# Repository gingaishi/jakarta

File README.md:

View this project on [CADLAB.io](https://cadlab.io/project/28195). 

# jakarta

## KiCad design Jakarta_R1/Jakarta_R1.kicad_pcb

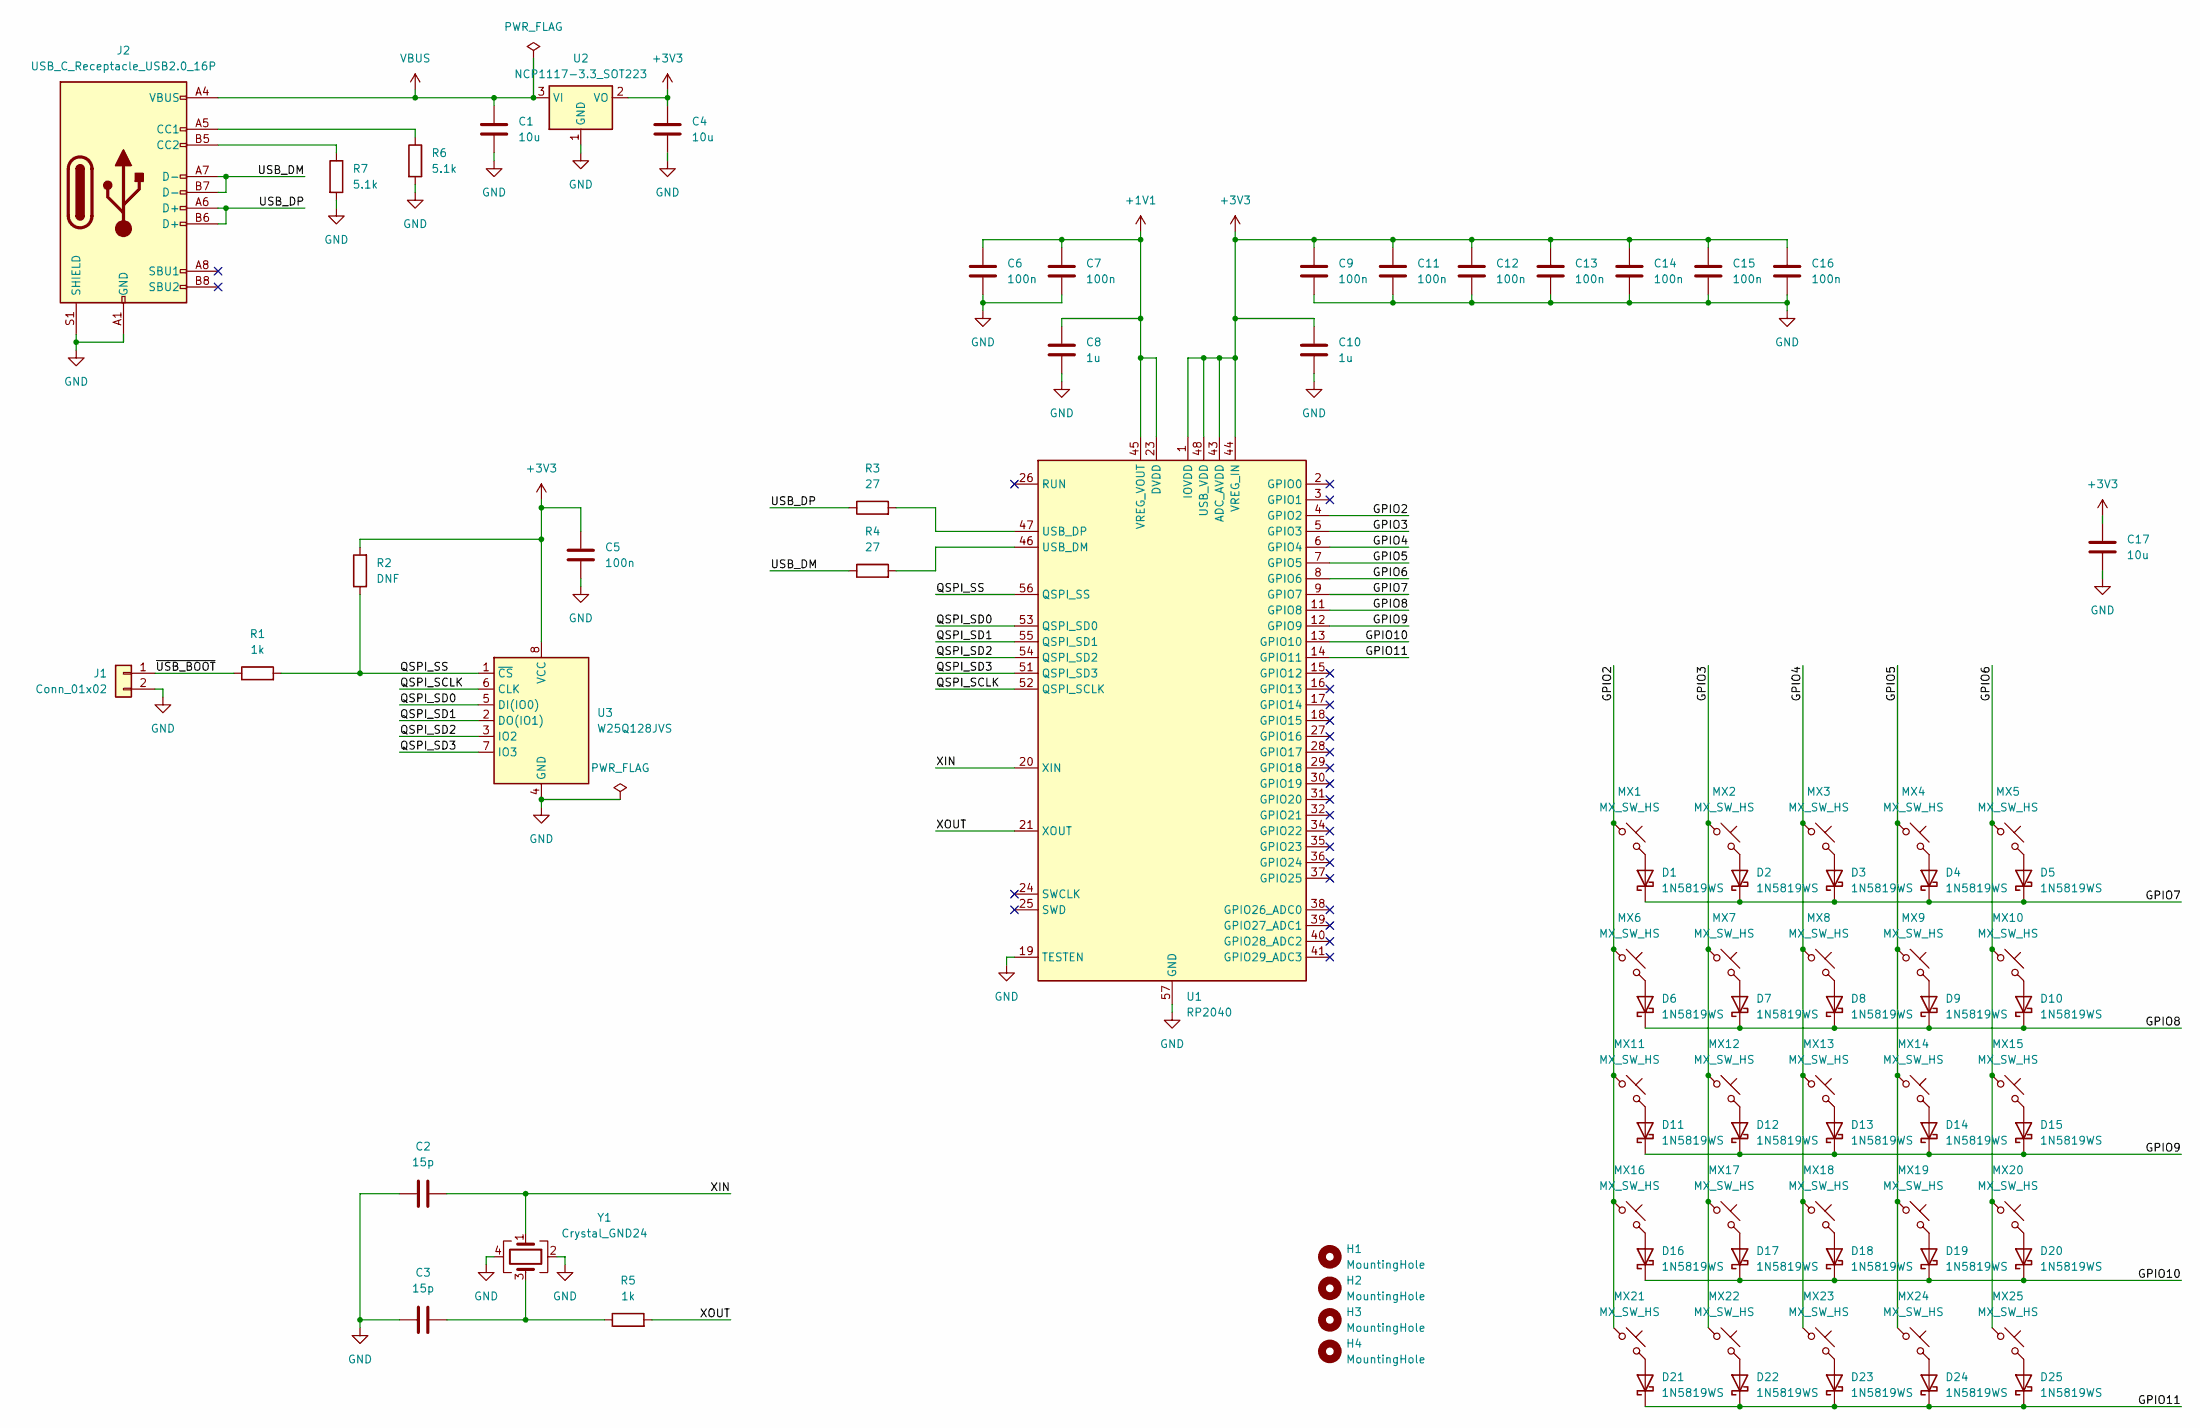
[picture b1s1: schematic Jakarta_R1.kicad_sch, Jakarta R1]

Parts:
C1, C4, C17: 10u; C_0805_2012Metric
C2, C3: 15p; C_0402_1005Metric
C5, C6, C7, C9, C11, C12, C13, C14, C15, C16: 100n; C_0402_1005Metric
C8, C10: 1u; C_0402_1005Metric
D1, D2, D3, D4, D5, D6, D7, D8, D9, D10, D11, D12, D13, D14, D15, D16, D17, D18, D19, D20, D21, D22, D23, D24, D25: 1N5819WS; D_SOD-323
H1, H2, H3, H4: MountingHole; MountingHole_3.2mm_M3
J1: Conn_01x02; PinHeader_1x02_P2.54mm_Vertical
J2: USB_C_Receptacle_USB2.0_16P; USB_C_Receptacle_GCT_USB4085
MX1, MX2, MX3, MX4, MX5, MX6, MX7, MX8, MX9, MX10, MX11, MX12, MX13, MX14, MX15, MX16, MX17, MX18, MX19, MX20, MX21, MX22, MX23, MX24, MX25: MX_SW_HS; SW_MX_HS_CPG151101S11_1u
R1, R5: 1k; R_0402_1005Metric
R2: DNF; R_0402_1005Metric
R3, R4: 27; R_0402_1005Metric
R6, R7: 5.1k; R_0402_1005Metric
U1: RP2040; QFN-56-1EP_7x7mm_P0.4mm_EP3.2x3.2mm
U2: NCP1117-3.3_SOT223; SOT-223-3_TabPin2
U3: W25Q128JVS; SOIC-8_5.23x5.23mm_P1.27mm
Y1: Crystal_GND24; Crystal_SMD_3225-4Pin_3.2x2.5mm

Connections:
+1V1: C6.1, C7.1, C8.1, U1.23 (DVDD), U1.45 (VREG_VOUT), U1.50 (DVDD)
+3V3: C4.1, C5.1, C9.1, C10.1, C11.1, C12.1, C13.1, C14.1, C15.1, C16.1, C17.1, R2.2, U1.1 (IOVDD), U1.10 (IOVDD), U1.22 (IOVDD), U1.33 (IOVDD), U1.42 (IOVDD), U1.43 (ADC_AVDD), U1.44 (VREG_IN), U1.48 (USB_VDD), U1.49 (IOVDD), U2.2 (VO), U3.8 (VCC)
/GPIO2: MX1.1, MX6.1, MX11.1, MX16.1, MX21.1, U1.4 (GPIO2)
/GPIO3: MX2.1, MX7.1, MX12.1, MX17.1, MX22.1, U1.5 (GPIO3)
/GPIO4: MX3.1, MX8.1, MX13.1, MX18.1, MX23.1, U1.6 (GPIO4)
/GPIO5: MX4.1, MX9.1, MX14.1, MX19.1, MX24.1, U1.7 (GPIO5)
/GPIO6: MX5.1, MX10.1, MX15.1, MX20.1, MX25.1, U1.8 (GPIO6)
/GPIO7: D1.1 (K), D2.1 (K), D3.1 (K), D4.1 (K), D5.1 (K), U1.9 (GPIO7)
/GPIO8: D6.1 (K), D7.1 (K), D8.1 (K), D9.1 (K), D10.1 (K), U1.11 (GPIO8)
/GPIO9: D11.1 (K), D12.1 (K), D13.1 (K), D14.1 (K), D15.1 (K), U1.12 (GPIO9)
/GPIO10: D16.1 (K), D17.1 (K), D18.1 (K), D19.1 (K), D20.1 (K), U1.13 (GPIO10)
/GPIO11: D21.1 (K), D22.1 (K), D23.1 (K), D24.1 (K), D25.1 (K), U1.14 (GPIO11)
/QSPI_SCLK: U1.52 (QSPI_SCLK), U3.6 (CLK)
/QSPI_SD0: U1.53 (QSPI_SD0), U3.5 (DI(IO0))
/QSPI_SD1: U1.55 (QSPI_SD1), U3.2 (DO(IO1))
/QSPI_SD2: U1.54 (QSPI_SD2), U3.3 (IO2)
/QSPI_SD3: U1.51 (QSPI_SD3), U3.7 (IO3)
/QSPI_SS: R1.2, R2.1, U1.56 (QSPI_SS), U3.1 (~CS)
/USB_DM: J2.A7 (D-), J2.B7 (D-), R4.1
/USB_DP: J2.A6 (D+), J2.B6 (D+), R3.1
/XIN: C2.2, U1.20 (XIN), Y1.1
/XOUT: R5.2, U1.21 (XOUT)
/~USB_BOOT: J1.1, R1.1
GND: C1.2, C2.1, C3.1, C4.2, C5.2, C6.2, C7.2, C8.2, C9.2, C10.2, C11.2, C12.2, C13.2, C14.2, C15.2, C16.2, C17.2, J1.2, J2.A1 (GND), J2.A12 (GND), J2.B1 (GND), J2.B12 (GND), J2.S1 (SHIELD), R6.2, R7.2, U1.19 (TESTEN), U1.57 (GND), U2.1 (GND), U3.4 (GND), Y1.2, Y1.4
unnamed: C3.2, R5.1, Y1.3
unnamed: D1.2 (A), MX1.2
unnamed: D2.2 (A), MX2.2
unnamed: D3.2 (A), MX3.2
unnamed: D4.2 (A), MX4.2
unnamed: D5.2 (A), MX5.2
unnamed: D6.2 (A), MX6.2
unnamed: D7.2 (A), MX7.2
unnamed: D8.2 (A), MX8.2
unnamed: D9.2 (A), MX9.2
unnamed: D10.2 (A), MX10.2
unnamed: D11.2 (A), MX11.2
unnamed: D12.2 (A), MX12.2
unnamed: D13.2 (A), MX13.2
unnamed: D14.2 (A), MX14.2
unnamed: D15.2 (A), MX15.2
unnamed: D16.2 (A), MX16.2
unnamed: D17.2 (A), MX17.2
unnamed: D18.2 (A), MX18.2
unnamed: D19.2 (A), MX19.2
unnamed: D20.2 (A), MX20.2
unnamed: D21.2 (A), MX21.2
unnamed: D22.2 (A), MX22.2
unnamed: D23.2 (A), MX23.2
unnamed: D24.2 (A), MX24.2
unnamed: D25.2 (A), MX25.2
unnamed: J2.A5 (CC1), R6.1
unnamed: J2.B5 (CC2), R7.1
unnamed: R4.2, U1.46 (USB_DM)
unnamed: R3.2, U1.47 (USB_DP)
VBUS: C1.1, J2.A4 (VBUS), J2.A9 (VBUS), J2.B4 (VBUS), J2.B9 (VBUS), U2.3 (VI)

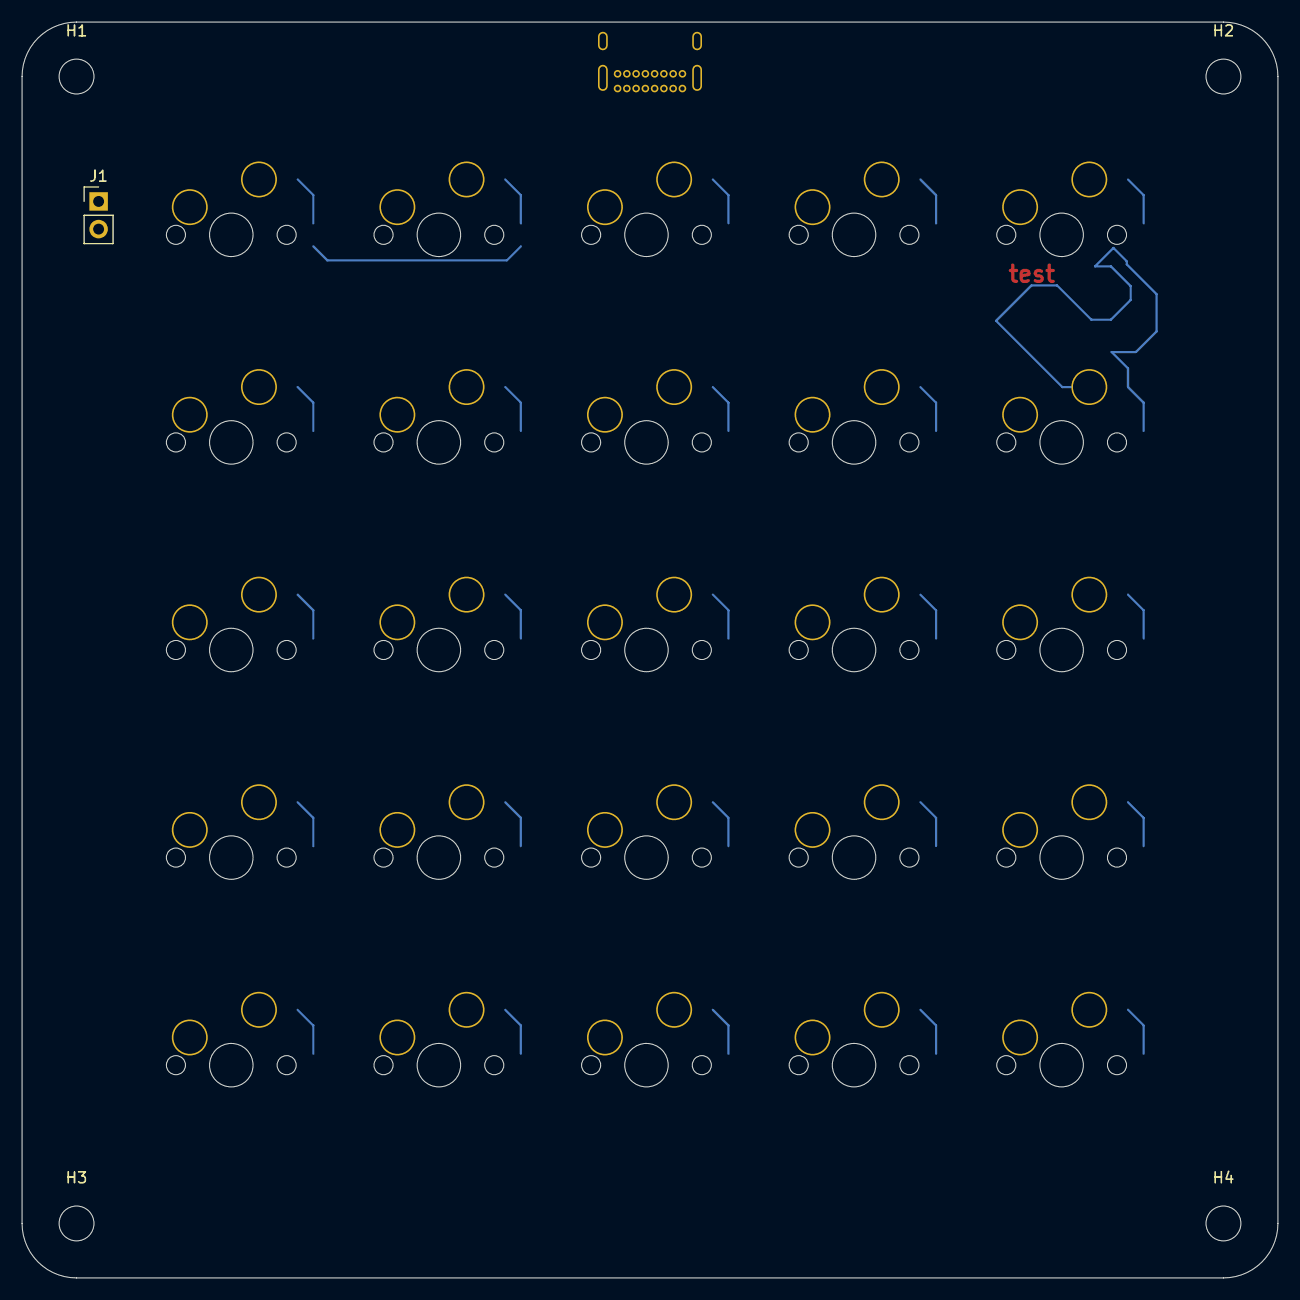
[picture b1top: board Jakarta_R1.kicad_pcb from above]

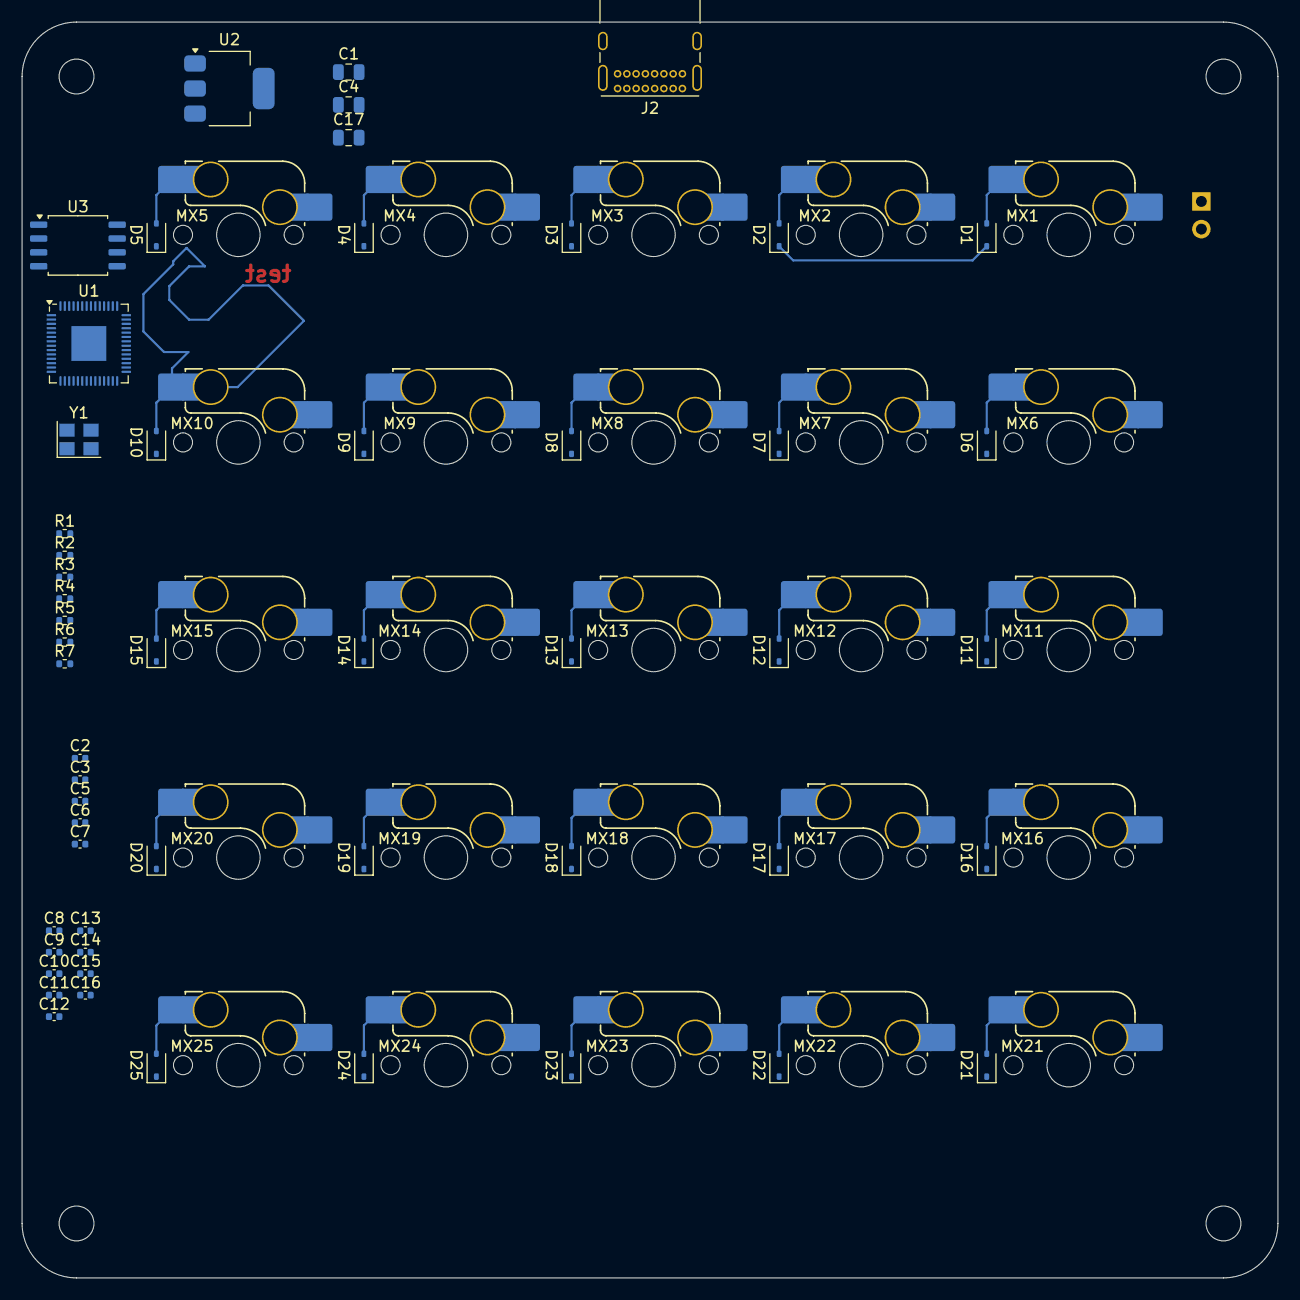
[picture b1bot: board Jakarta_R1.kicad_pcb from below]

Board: 2 copper layers, 115.2 x 115.2 mm, 84 parts (79 on the bottom side), 55 nets.

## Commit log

2024-06-15 Backlink to CADLAB.io has been added.
2024-06-16 test
